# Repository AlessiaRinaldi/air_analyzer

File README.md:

## Documentation

The full project documentation is available at:

[Air Analyzer Documentation](https://alessiarinaldi.github.io/air_analyzer/)

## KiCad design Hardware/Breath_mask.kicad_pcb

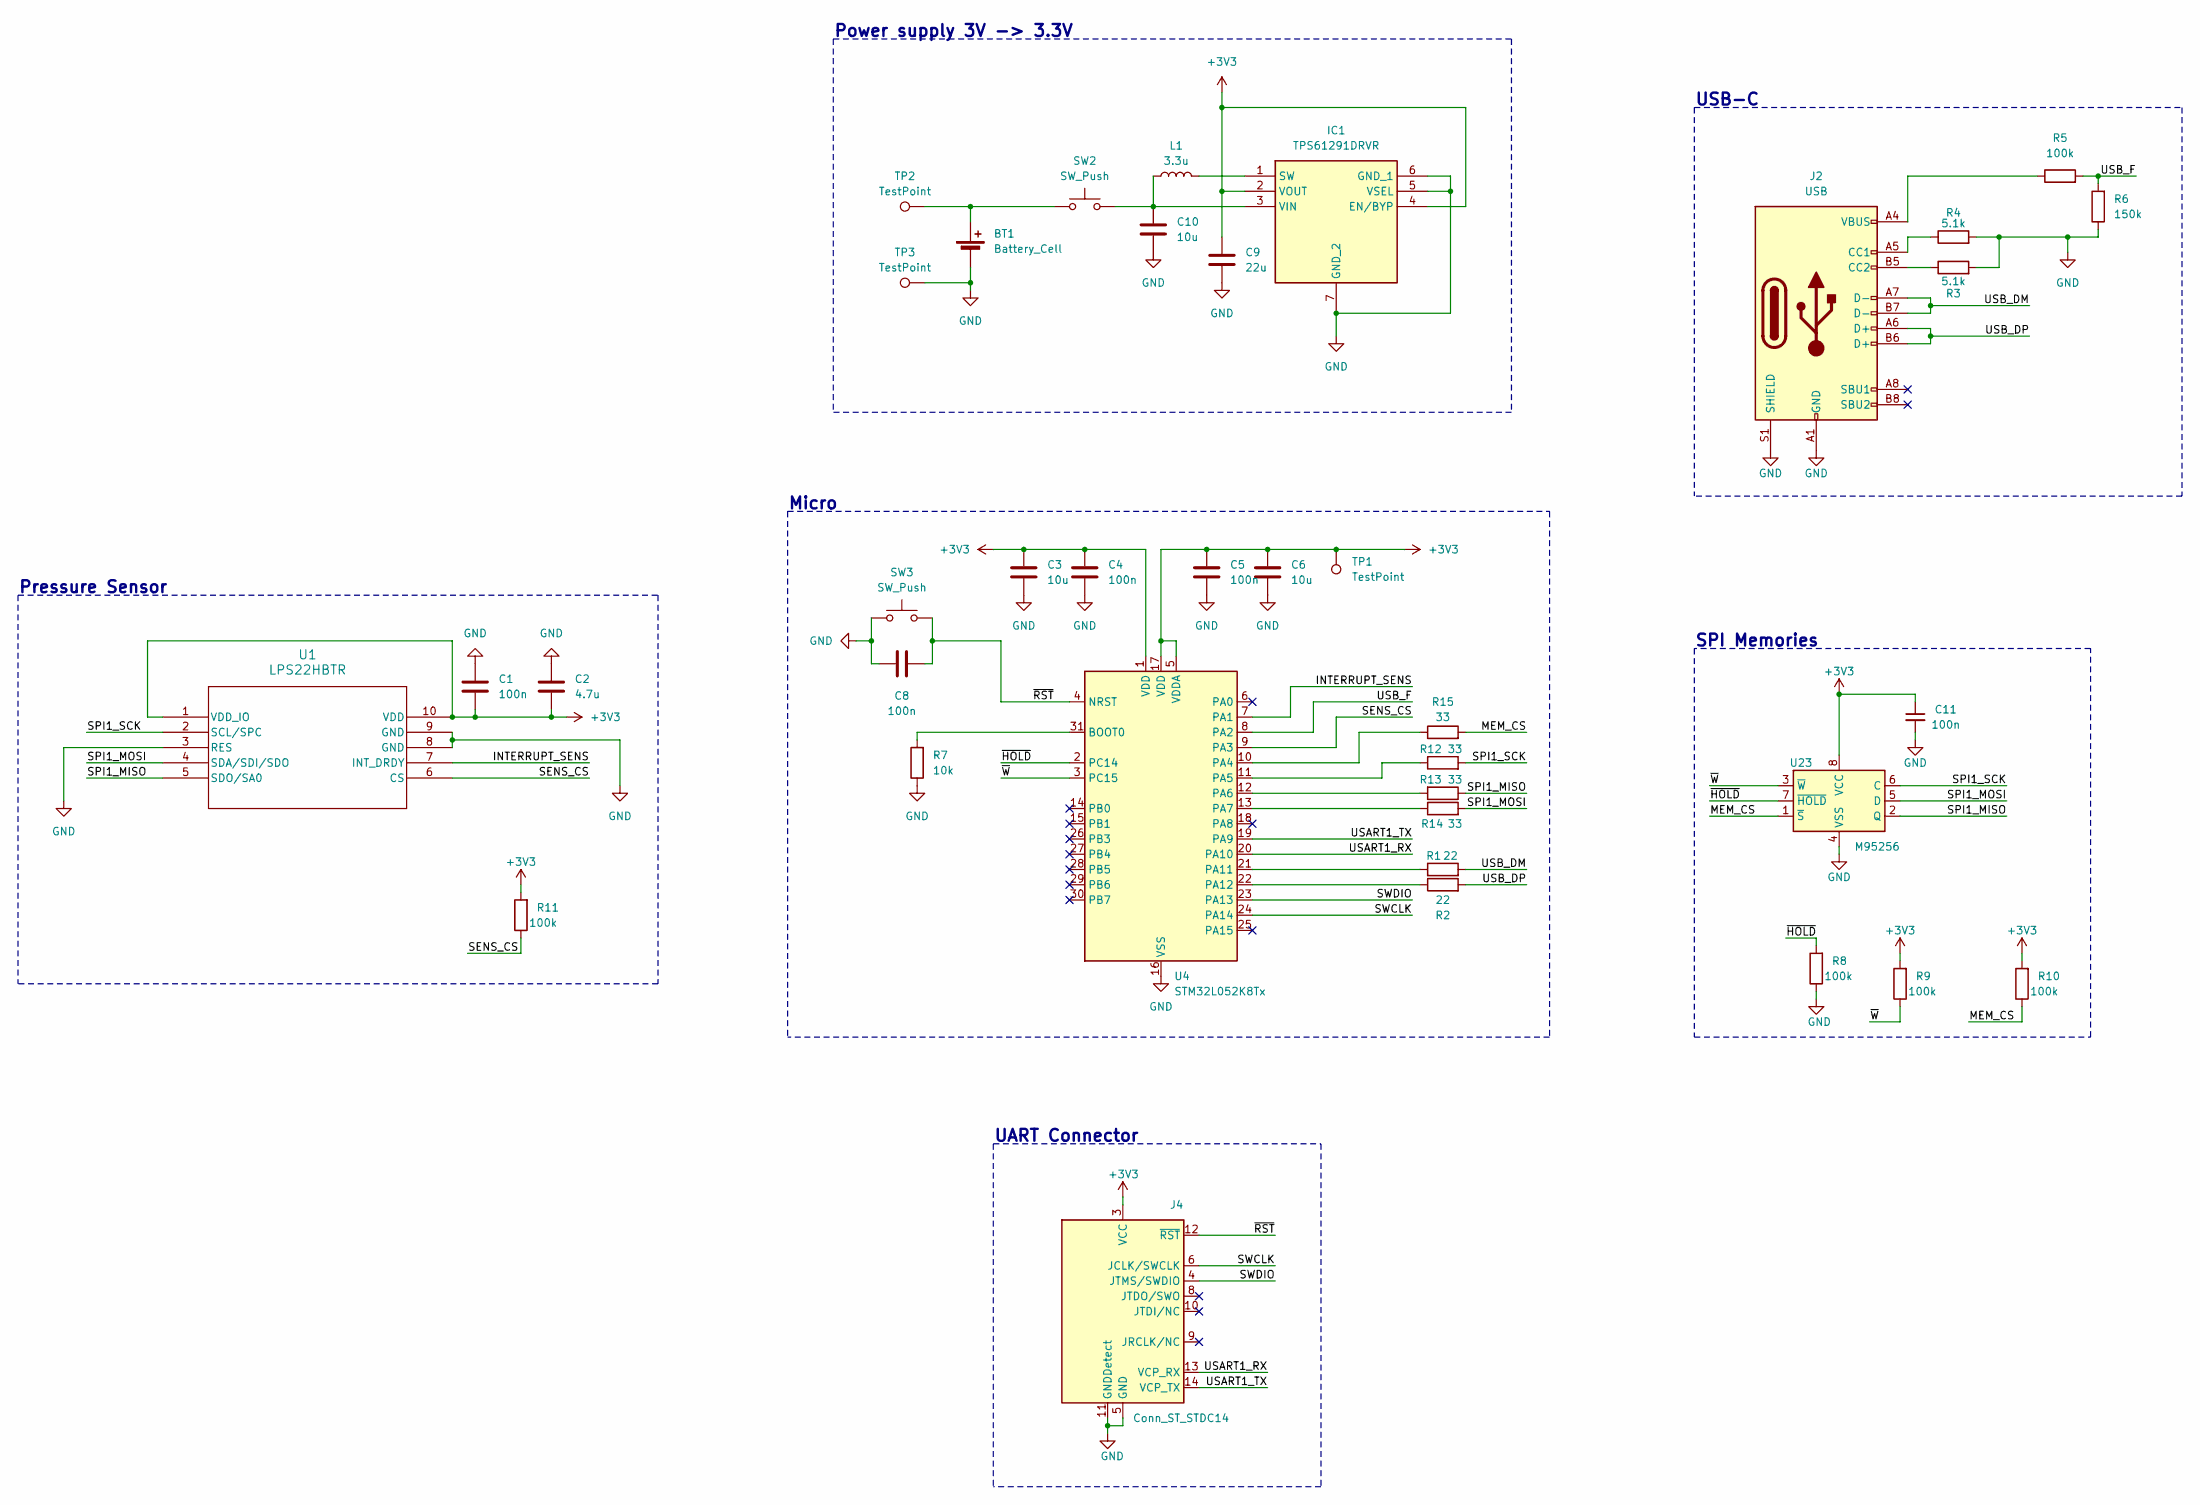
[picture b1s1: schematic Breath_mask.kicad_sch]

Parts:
BT1: Battery_Cell; BatteryHolder_Keystone_3034_1x20mm
C1, C4, C5, C8, C11: 100n; C_0603_1608Metric
C2: 4.7u; C_0603_1608Metric
C3, C6, C10: 10u; C_0805_2012Metric
C9: 22u; C_0805_2012Metric
IC1: TPS61291DRVR; WSON-6-1EP_2x2mm_P0.65mm_EP1x1.6mm_ThermalVias; Mouser Part Number 595-TPS61291DRVR
J2: USB; USB_C_Receptacle_HRO_TYPE-C-31-M-12
J4: Conn_ST_STDC14; SAMTEC_FTSH-107-01-L-DV-K-TR
L1: 3.3u; L_Coilcraft_LPS3314
R1, R2: 22; R_0603_1608Metric
R3, R4: 5.1k; R_0603_1608Metric
R5, R8, R9, R10, R11: 100k; R_0603_1608Metric
R6: 150k; R_0603_1608Metric
R7: 10k; R_0603_1608Metric
R12, R13, R14, R15: 33; R_0603_1608Metric
SW2: SW_Push; SW_SPDT_CK_JS102011SAQN
SW3: SW_Push; SW_Push_1P1T_XKB_TS-1187A
TP1, TP2, TP3: TestPoint; TestPoint_Pad_D1.0mm
U1: LPS22HBTR; ST_HLGA-10_2x2mm_P0.5mm_LayoutBorder3x2y
U4: STM32L052K8Tx; LQFP-32_7x7mm_P0.8mm; LCSC C222404
U23: M95256; TSSOP-8_4.4x3mm_P0.65mm

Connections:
+3V3: C1.2, C2.2, C3.2, C4.2, C5.2, C6.2, C9.1, C11.1, IC1.2 (VOUT), IC1.4 (EN/BYP), J4.3 (VCC), R9.2, R10.2, R11.2, TP1.1 (1_1), U1.1 (VDD_IO), U1.10 (VDD), U4.1 (VDD), U4.5 (VDDA), U4.17 (VDD), U23.8 (VCC)
/INTERRUPT_SENS: U1.7 (INT_DRDY), U4.7 (PA1)
/MEM_CS: R10.1, R15.2, U23.1 (~S)
/SENS_CS: R11.1, U1.6 (CS), U4.9 (PA3)
/SPI1_MISO: R13.1, U1.5 (SDO/SA0), U23.2 (Q)
/SPI1_MOSI: R14.2, U1.4 (SDA/SDI/SDO), U23.5 (D)
/SPI1_SCK: R12.2, U1.2 (SCL/SPC), U23.6 (C)
/SWCLK: J4.6 (JCLK/SWCLK), U4.24 (PA14)
/SWDIO: J4.4 (JTMS/SWDIO), U4.23 (PA13)
/USART1_RX: J4.13 (VCP_RX), U4.20 (PA10)
/USART1_TX: J4.14 (VCP_TX), U4.19 (PA9)
/USB_DM: J2.A7 (D-), J2.B7 (D-), R1.2
/USB_DP: J2.A6 (D+), J2.B6 (D+), R2.2
/USB_F: R5.2, R6.2, U4.8 (PA2)
/~HOLD: R8.2, U4.2 (PC14), U23.7 (~HOLD)
/~RST: C8.2, J4.12 (~RST), SW3.2, U4.4 (NRST)
/~W: R9.1, U4.3 (PC15), U23.3 (~W)
GND: BT1.2 (-), C1.1, C2.1, C3.1, C4.1, C5.1, C6.1, C8.1, C9.2, C10.2, C11.2, IC1.5 (VSEL), IC1.6 (GND_1), IC1.7 (GND_2), J2.A1 (GND), J2.A12 (GND), J2.B1 (GND), J2.B12 (GND), J2.S1 (SHIELD), J4.5 (GND), J4.7 (GND), J4.11 (GNDDetect), R3.2, R4.2, R6.1, R7.1, R8.1, SW3.1, TP3.1 (1_1), U1.3 (RES), U1.8 (GND), U1.9 (GND), U4.16 (VSS), U4.32 (VSS), U23.4 (VSS)
unnamed: BT1.1 (+), SW2.1, TP2.1 (1_1)
unnamed: IC1.1 (SW), L1.2
unnamed: C10.1, IC1.3 (VIN), L1.1, SW2.2
unnamed: J2.A5 (CC1), R4.1
unnamed: J2.B5 (CC2), R3.1
unnamed: J2.A4 (VBUS), J2.A9 (VBUS), J2.B4 (VBUS), J2.B9 (VBUS), R5.1
unnamed: R7.2, U4.31 (BOOT0)
unnamed: R15.1, U4.10 (PA4)
unnamed: R12.1, U4.11 (PA5)
unnamed: R13.2, U4.12 (PA6)
unnamed: R14.1, U4.13 (PA7)
unnamed: R1.1, U4.21 (PA11)
unnamed: R2.1, U4.22 (PA12)

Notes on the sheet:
Pressure Sensor
UART Connector
USB-C
Micro
SPI Memories
Power supply 3V -> 3.3V

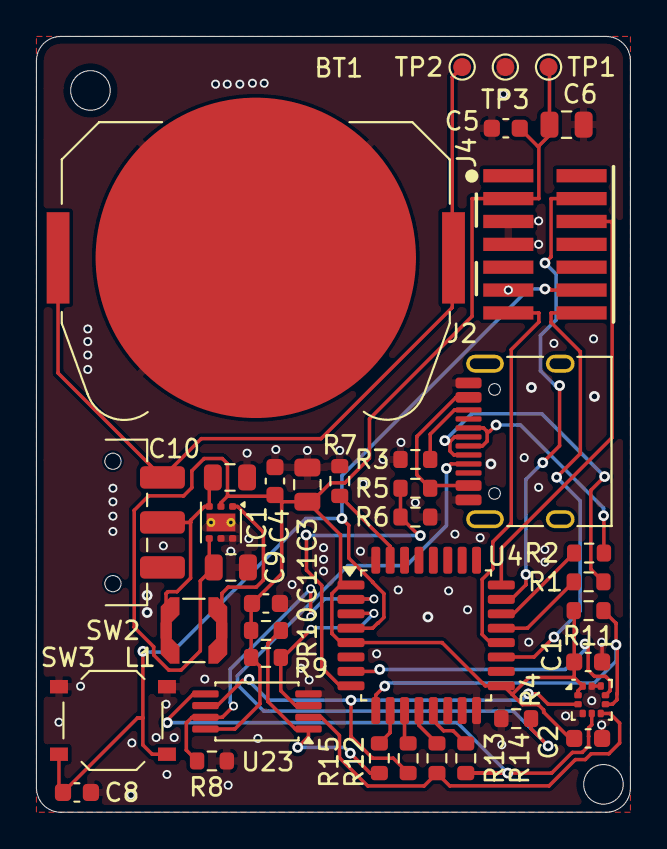
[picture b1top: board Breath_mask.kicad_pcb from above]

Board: 2 copper layers, 33.0 x 43.1 mm, 38 parts (0 on the bottom side), 31 nets.

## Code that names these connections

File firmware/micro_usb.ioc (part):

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Mcu.Name=STM32L052K(6-8)Tx
Mcu.Package=LQFP32
Mcu.UserName=STM32L052K8Tx
PA1.GPIOParameters=GPIO_Label
PA1.GPIO_Label=INTERRUPT_SENS
PA1.Signal=GPIO_Input
PA10.Mode=Asynchronous
PA10.Signal=USART1_RX
PA11.Mode=Device
PA11.Signal=USB_DM
PA12.Mode=Device
PA12.Signal=USB_DP
PA13.Mode=Serial_Wire
PA13.Signal=SYS_SWDIO
PA14.Mode=Serial_Wire
PA14.Signal=SYS_SWCLK
PA2.GPIOParameters=GPIO_Label
PA2.GPIO_Label=USBC_F
PA2.Signal=GPIO_Input
PA3.GPIOParameters=GPIO_Label
PA3.GPIO_Label=SENS_CSS
PA3.Signal=GPIO_Output
PA4.GPIOParameters=GPIO_Label
PA4.GPIO_Label=MEM_CSN
PA4.Signal=GPIO_Output
PA5.Mode=Full_Duplex_Master
PA5.Signal=SPI1_SCK
PA6.Mode=Full_Duplex_Master
PA6.Signal=SPI1_MISO
PA7.Mode=Full_Duplex_Master
PA7.Signal=SPI1_MOSI
PA9.Mode=Asynchronous
PA9.Signal=USART1_TX
PC14-OSC32_IN.GPIOParameters=GPIO_Label
PC14-OSC32_IN.GPIO_Label=NOT_HOLD
PC14-OSC32_IN.Signal=GPIO_Output
PC15-OSC32_OUT.GPIOParameters=GPIO_Label
PC15-OSC32_OUT.GPIO_Label=NOT_W
PC15-OSC32_OUT.Signal=GPIO_Output
RCC.SYSCLKFreq_VALUE=16000000
RCC.SYSCLKSource=RCC_SYSCLKSOURCE_HSI
board=custom

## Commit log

2025-10-11 Added datasheet
2026-04-01 setup schematic
2026-04-03 inizio sbroglio pcb
2026-04-13 Aggiornamento sbroglio
2026-04-14 dimensions fixed without traces
2026-04-14 Aggiornamento sbroglio con tool
2026-04-14 Sbroglio con tool
2026-04-14 errors fixed
2026-04-21 firmware: initialized
2026-05-16 Correzione main dopo rollback
2026-05-16 ignora cartella vscode locale
2026-05-16 quarto documentation
2026-05-18 code fixed
2026-05-19 quarto changes
2026-05-19 Initializing gh-pages branch
2026-05-19 Built site for gh-pages
2026-05-20 website modified
2026-06-17 topics reordered
2026-06-18 website updated
2026-06-18 presentation added
